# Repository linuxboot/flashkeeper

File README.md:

# Flashkeeper

## Manage and Protect your SPI Flash Chip!

[Documentation](https://flashkeeper.org) | [Source](https://git.15h.org/Flashkeeper/flashkeeper) | [Join us on Matrix!](https://matrix.to/#/#flashkeeper:matrix.org)

Flashkeeper is a family of open-hardware add-ons for standard SOIC-8 and WSON-8 SPI NOR flash chips (as are commonly used for firmware storage in PCs and other electronics), providing functionality for write-protection control, SPI bus breakout, flash device emulation, reprogramming, and state validation.

Flashkeeper development takes place on the [15h.org](https://15h.org) Git forge, and is mirrored to Github as a backup. If you wish to participate in Flashkeeper development on 15h.org infrastructure, please request an account in either the [Flashkeeper room](https://matrix.to/#/#flashkeeper:matrix.org) or the 15h.org room on Matrix. Issues may be opened on either 15h.org or Github.

For user information, please see the [documentation](https://flashkeeper.org). For hardware source files, see `hw/`.

The Flashkeeper project is supported by [NLnet NGI Zero Core](https://nlnet.nl/project/Flashkeeper/).

---

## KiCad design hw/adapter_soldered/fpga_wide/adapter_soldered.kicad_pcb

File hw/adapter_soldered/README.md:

# Soldered Chip Adapter

`wp_only_wide`: Write-protect-only chip adapter, controls flash chip write protect using switch or solder jumper, for wide (standard for flash chips) SOIC-8 and WSON-8.

`wp_only`: Same as above, for (rare for flash chips) "narrow" SOIC-8 packages

`breakout_wide`: Breakout chip adapter, for connecting your flash chip to external hardware (like a programmer or an SPIspy device) using a 0.5mm 8-pin FFC. For wide SOIC-8 and WSON-8.

`integrated_cable`: Experimental. Like the breakout adapter, but rather than having an FFC ZIF socket like the above, it has a short length of FFC built-in.

`adapter_soldered.kicad_pro` Overarching KiCAD project containing all variants. Use of this is optional.

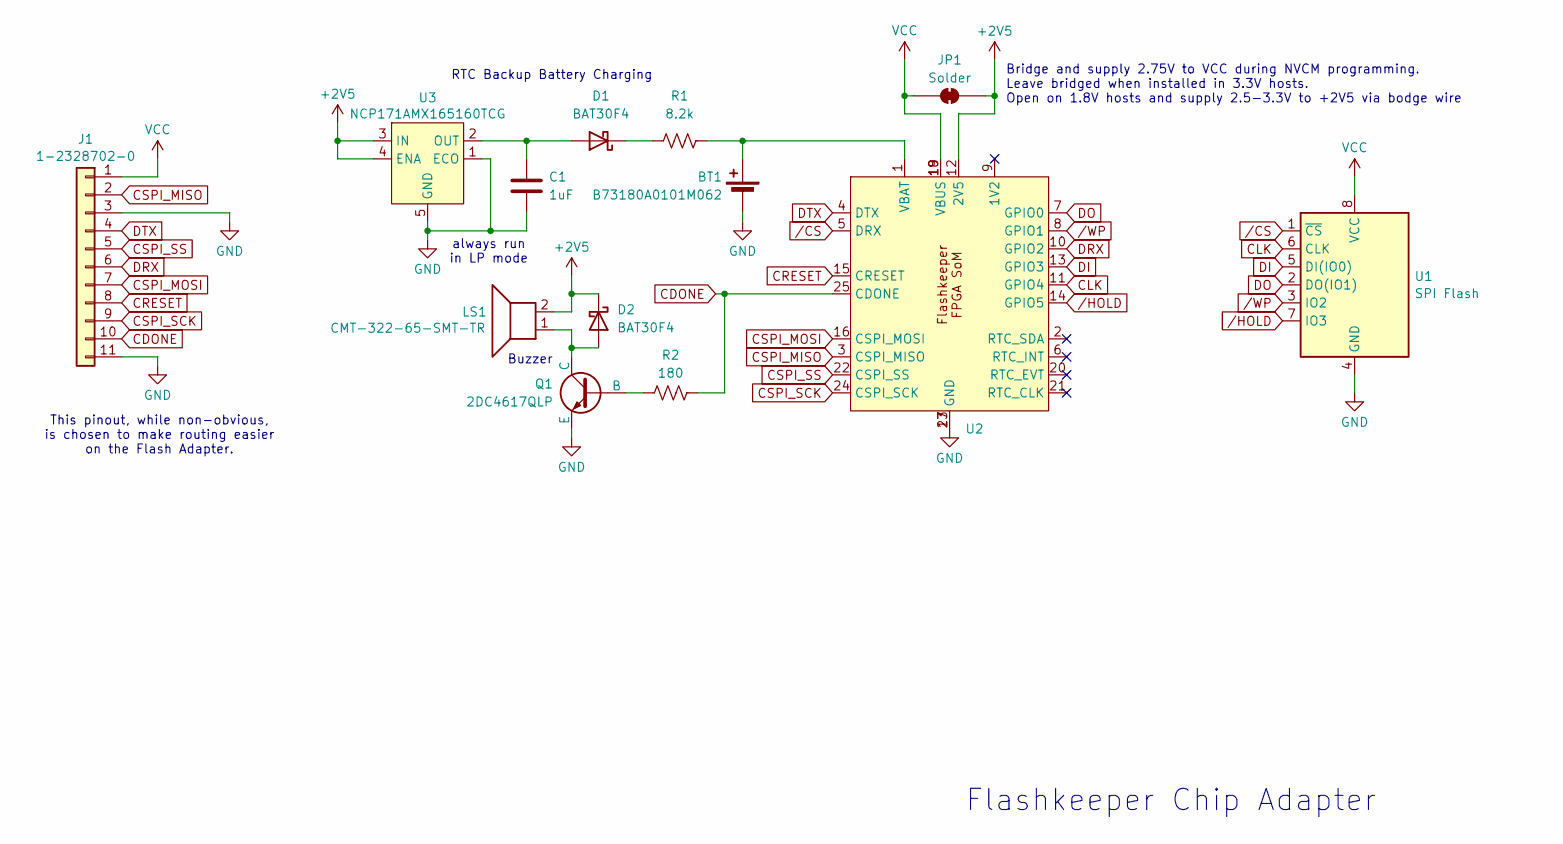
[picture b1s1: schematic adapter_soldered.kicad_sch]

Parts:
BT1: B73180A0101M062; C_1812_4532Metric
C1: 1uF; C_0201_0603Metric
D1, D2: BAT30F4; D_0201_0603Metric
J1: 1-2328702-0; TE_1-2328702-0
JP1: Solder; SolderJumper_0.4mm
LS1: CMT-322-65-SMT-TR; XDCR_CMT-322-65-SMT-TR
Q1: 2DC4617QLP; Diodes_DFN1006-3
R1: 8.2k; R_0201_0603Metric
R2: 180; R_0201_0603Metric
U1: SPI Flash; SolderConnector_SOIC8Wide_1.5mmLift
U2: FlashkeeperFPGASoM_ReducedPins
U3: NCP171AMX165160TCG; VREG_NCP171AMX180175TCG

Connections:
+2V5: D2.1 (K), JP1.2 (B), LS1.2, U2.12 (2V5), U3.3 (IN), U3.4 (ENA)
CDONE: J1.10, R2.2, U2.25 (CDONE)
CLK: U1.6 (CLK), U2.11 (GPIO4)
CRESET: J1.8, U2.15 (CRESET)
CSPI_MISO: J1.2, U2.3 (CSPI_MISO)
CSPI_MOSI: J1.7, U2.16 (CSPI_MOSI)
CSPI_SCK: J1.9, U2.24 (CSPI_SCK)
CSPI_SS: J1.5, U2.22 (CSPI_SS)
DI: U1.5 (DI(IO0)), U2.13 (GPIO3)
DO: U1.2 (DO(IO1)), U2.7 (GPIO0)
DRX: J1.6, U2.10 (GPIO2)
DTX: J1.4, U2.4 (DTX)
GND: BT1.2 (-), C1.2, J1.3, J1.11, Q1.3 (E), U1.4 (GND), U2.17 (GND), U2.23 (GND), U3.1 (ECO), U3.5 (GND)
unnamed: BT1.1 (+), R1.2, U2.1 (VBAT)
unnamed: C1.1, D1.2 (A), U3.2 (OUT)
unnamed: D1.1 (K), R1.1
unnamed: D2.2 (A), LS1.1, Q1.1 (C)
unnamed: Q1.2 (B), R2.1
VCC: J1.1, JP1.1 (A), U1.8 (VCC), U2.18 (VBUS), U2.19 (VBUS)
/CS: U1.1 (~CS), U2.5 (DRX)
/HOLD: U1.7 (IO3), U2.14 (GPIO5)
/WP: U1.3 (IO2), U2.8 (GPIO1)

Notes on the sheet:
RTC Backup Battery Charging
Flashkeeper Chip Adapter
always run in LP mode
Bridge and supply 2.75V to VCC during NVCM programming. Leave bridged when installed in 3.3V hosts. Open on 1.8V hosts and supply 2.5-3.3V to +2V5 via bodge wire
Buzzer
This pinout, while non-obvious, is chosen to make routing easier on the Flash Adapter.

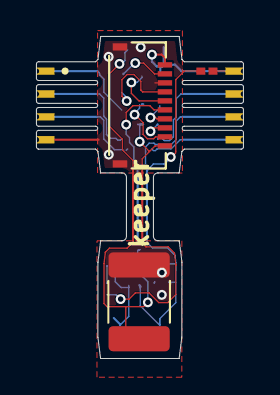
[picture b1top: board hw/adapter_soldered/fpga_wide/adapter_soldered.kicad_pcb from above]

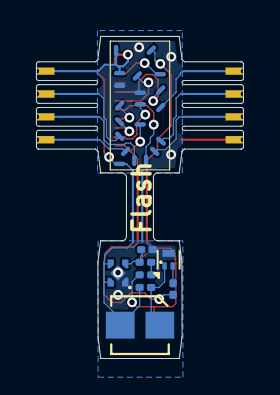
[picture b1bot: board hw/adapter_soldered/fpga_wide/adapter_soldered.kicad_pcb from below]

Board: 2 copper layers, 11.5 x 17.9 mm, 13 parts (9 on the bottom side), 22 nets.

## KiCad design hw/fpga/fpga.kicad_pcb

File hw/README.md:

# Flashkeeper Hardware
For source of the Flashkeeper website, see https://github.com/linuxboot/flashkeeper.

`adapter_soldered`: KiCAD files for the soldered Flashkeeper chip adapter

`dummy_board`: Rigid PCB with multiple flash package footprints and connectors for testing and development

`spispy_board`: FPGA-SoM-based board to run `spispy` during development

`single_stencil`: Project containing all PCBs in a single file. Intended to export a single paste-layer Gerber so that all Flashkeeper boards can be made using different parts of a single solder paste stencil.

`CAD`: FreeCAD files for Flashkeeper mechanical components

`flashkeeper.kicad_sym`: Symbol library for components used in Flashkeeper

`flashkeeper.pretty`: Footprint library for components used in Flashkeeper

KiCAD and FreeCAD files are for the latest upstream versions of KiCAD and FreeCAD, as of the last modification of that file. Depending on which versions your OS's packages ship, on some platforms (like Debian), this may mean installing from another repository (e.g. Debian Backports), or using an alternative packaging system such as Flatpak or AppImage. Please follow the installation instructions for your platform here:

- https://www.kicad.org/download/

- https://www.freecad.org/downloads.php

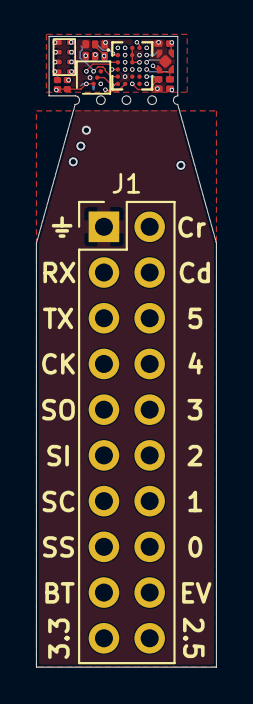
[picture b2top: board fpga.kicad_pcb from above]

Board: 6 copper layers, 10.0 x 35.0 mm, 37 parts (0 on the bottom side), 24 nets.

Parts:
C1, C2, C3, C4: 4.7 uF; C_Smaller_0201
J1: Conn_02x09_Odd_Even; PinHeader_2x10_P2.54mm_Vertical
R1: 10k; R_Smaller_0201
R3: 100; R_Smaller_0201
RN1: 10k; YC102
TP1, TP2, TP3, TP4, TP5, TP6, TP7, TP8, TP9, TP10, TP11, TP12, TP13, TP14, TP15, TP16, TP17, TP18, TP19, TP20, TP21, TP23, TP24, TP25, TP26: FPGACenterPad
U1: ICE40UP5K-UWG30ITR; BGA30N40P5X6_253X211X60N
U2: TPS7A2012PDQNR; Texas_X2SON-4_1x1mm_P0.65mm
U3: AT25DF041B-UUN-T; WLCSP-8_1.58x1.63x0.35mm_Layout3x5_P0.35x0.4mm_Ball0.25mm_P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
U4: RV-3028-C8

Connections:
+1V2: C2.1, R3.1, TP20.1, U1.C2 (VCC), U2.1 (OUT)
+2V5: C4.2, J1.20, TP19.1, U1.D4 (VPP_2V5)
CDONE: J1.4, TP1.1, U1.D3 (IOB_12A/G4_~CDONE)
CLK: J1.7, TP11.1, U1.F2 (IOB_25B/G3), U4.1 (CLKOUT)
CRESET: J1.2, R1.2, TP18.1, U1.F3 (~CRESET_B)
CSPI_MISO: J1.11, TP13.1, U1.E1 (IOB_33B/SPI_SI), U3.C3 (SO/IO1)
CSPI_MOSI: J1.9, TP12.1, U1.F1 (IOB_32A/SPI_SO), U3.D2 (SI/IO0)
CSPI_SCK: J1.13, TP14.1, U1.D1 (IOB_34A/SPI_SCK), U3.E1 (SCK), U4.3 (SCL)
CSPI_SS: J1.15, RN1.4 (R2.2), TP15.1, U1.C1 (IOB_35B/SPI_SS_B), U3.A3 (~CS)
DRX: J1.3, TP10.1, U1.A1 (IOT_36B)
DTX: J1.5, TP17.1, U1.B1 (IOB_24A)
EVT: J1.18, RN1.2 (R1.2), TP23.1, U4.8 (EVI)
GND: C1.2, C2.2, C3.1, C4.1, J1.1, TP16.1, TP25.1, U1.B4 (GND), U1.E2 (GND), U2.2 (GND), U2.5 (Pad), U3.B2 (GND), U4.5 (VSS)
GPIO0: J1.16, TP2.1, U1.A5 (RGB0)
GPIO1: J1.14, TP3.1, U1.B5 (RGB1)
GPIO2: J1.12, TP4.1, U1.C5 (RGB2)
GPIO3: J1.10, TP5.1, U1.E5 (IOB_0A)
GPIO4: J1.8, TP6.1, U1.D5 (IOB_2A)
GPIO5: J1.6, TP7.1, U1.F5 (IOB_3B/G6)
unnamed: C1.1, R3.2, U1.B2 (VCCPLL)
RTC_INT: TP8.1, U1.A4 (IOT_47A), U4.2 (~INT)
RTC_SDA: TP24.1, U1.A2 (IOT_37A), U4.4 (SDA)
VBAT: J1.17, TP21.1, U4.6 (VBACKUP)
VBUS: C3.2, J1.19, R1.1, RN1.1 (R1.1), RN1.3 (R2.1), TP9.1, TP26.1, U1.A3 (VCCIO_0), U1.B3 (IOT_46B/G0), U1.C3 (IOB_10A), U1.C4 (VCCIO_2), U1.D2 (SPI_VCCIO1), U2.3 (EN), U2.4 (IN), U3.A1 (VCC), U3.C1 (~HOLD), U4.7 (VDD)

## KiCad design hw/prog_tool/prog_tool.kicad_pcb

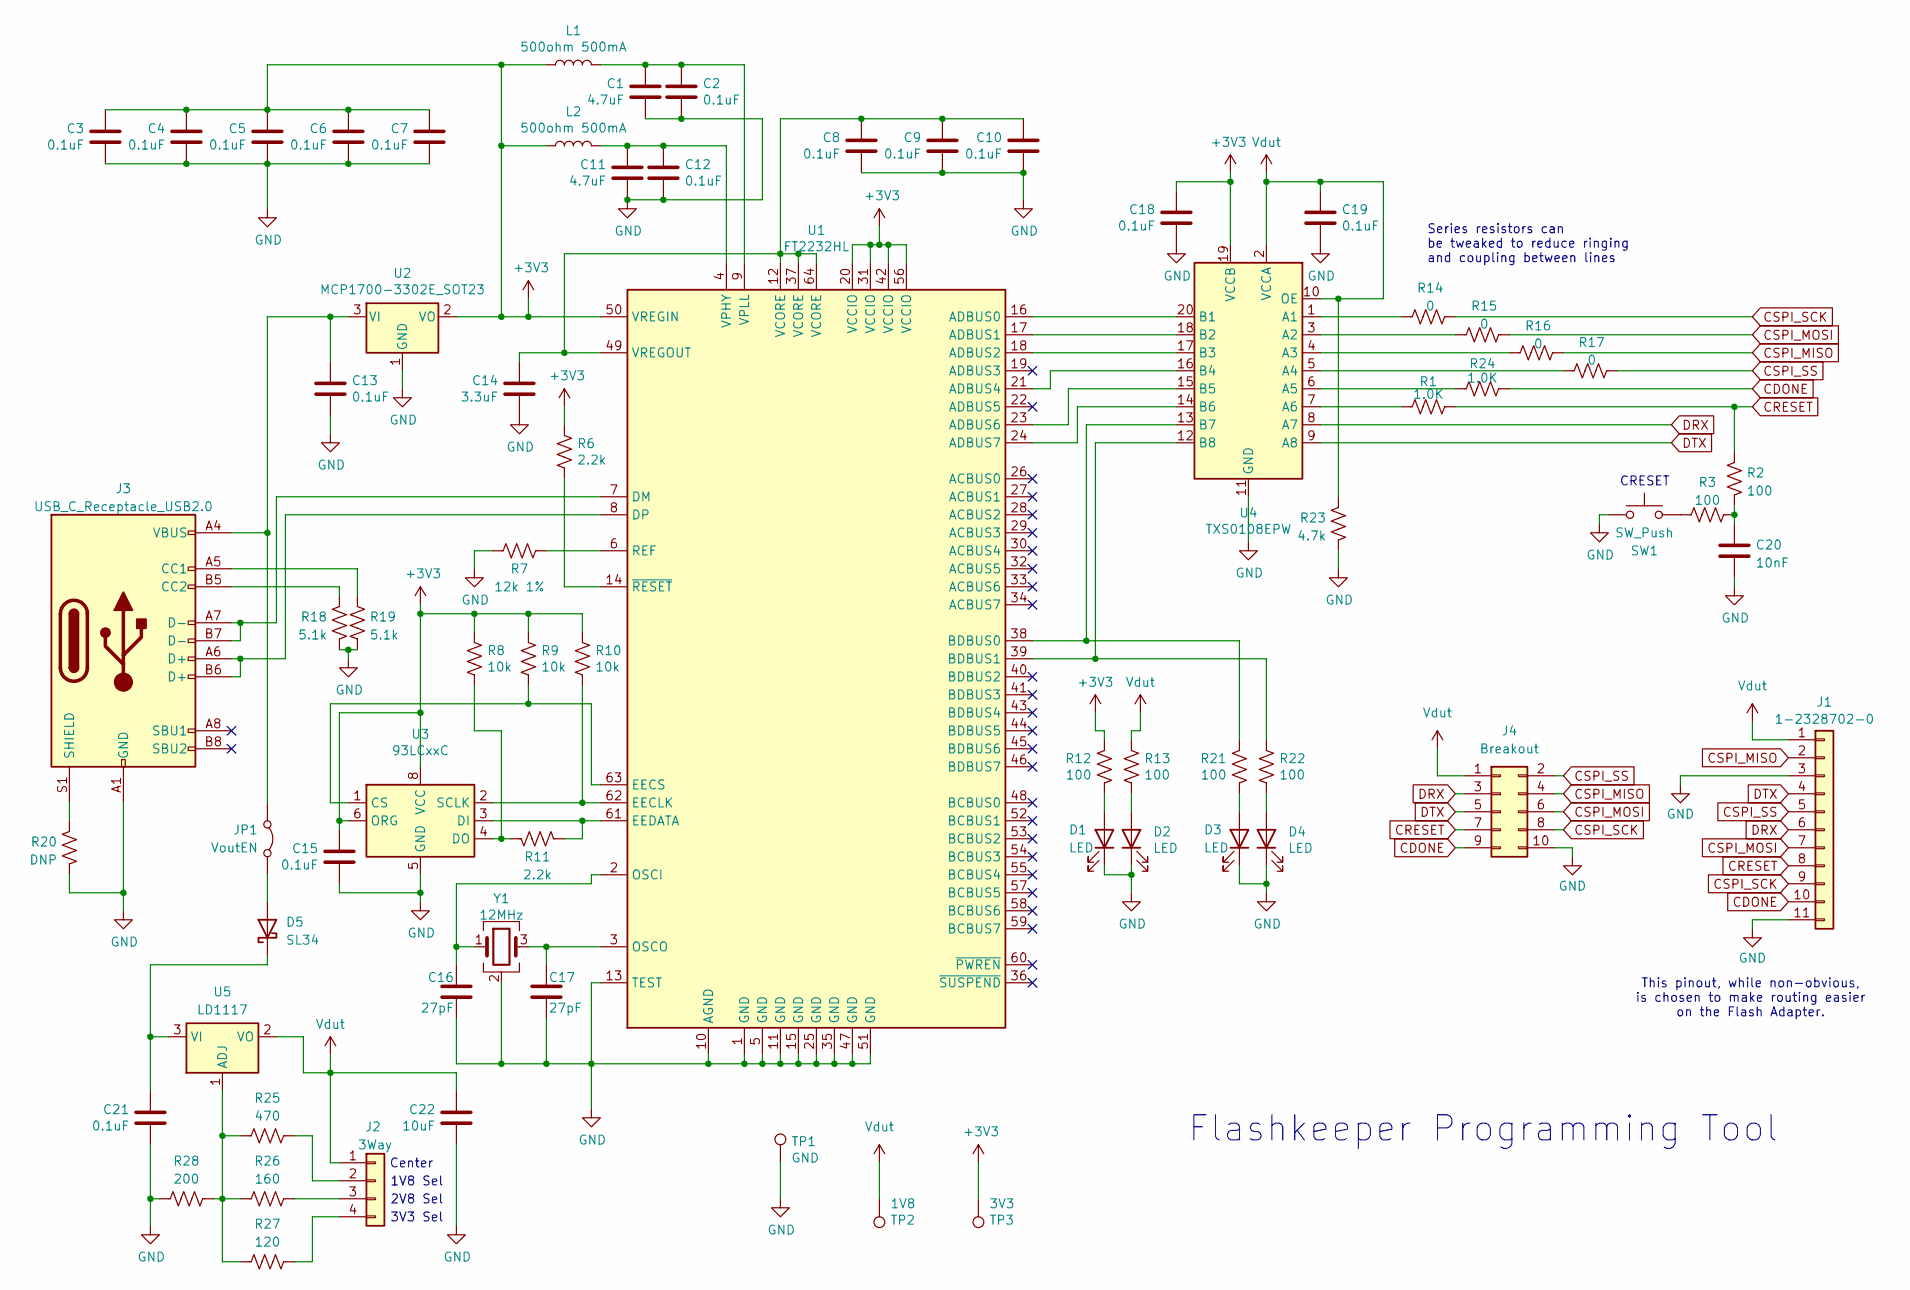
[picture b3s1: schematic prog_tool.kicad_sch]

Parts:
C1, C11: 4.7uF; C_0603_1608Metric
C2, C3, C4, C5, C6, C7, C8, C9, C10, C12, C13, C15, C18, C19, C21: 0.1uF; C_0603_1608Metric
C14: 3.3uF; C_0603_1608Metric
C16, C17: 27pF; C_0603_1608Metric
C20: 10nF; C_0603_1608Metric
C22: 10uF; C_0603_1608Metric
D1, D2, D3, D4: LED; LED_0603_1608Metric
D5: SL34; D_SMA
J1: 1-2328702-0; TE_1-2328702-0
J2: 3Way; ThreeWayJumper
J3: USB_C_Receptacle_USB2.0; USB4215-03-A
J4: Breakout; PinHeader_2x05_P2.54mm_Vertical
JP1: VoutEN; PinHeader_1x02_P2.54mm_Vertical
L1, L2: 500ohm 500mA; L_0603_1608Metric
R1, R24: 1.0K; R_0603_1608Metric
R2, R3, R12, R13, R21, R22: 100; R_0603_1608Metric
R6, R11: 2.2k; R_0603_1608Metric
R7: 12k 1%; R_0603_1608Metric
R8, R9, R10: 10k; R_0603_1608Metric
R14, R15, R16, R17: 0; R_0603_1608Metric
R18, R19: 5.1k; R_0603_1608Metric
R20: DNP; R_0603_1608Metric
R23: 4.7k; R_0603_1608Metric
R25: 470; R_0603_1608Metric
R26: 160; R_0603_1608Metric
R27: 120; R_0603_1608Metric
R28: 200; R_0603_1608Metric
SW1: SW_Push; SW_PUSH_6mm
TP1: GND; TestPoint_THTPad_2.0x2.0mm_Drill1.0mm
TP2: 1V8; TestPoint_THTPad_2.0x2.0mm_Drill1.0mm
TP3: 3V3; TestPoint_THTPad_2.0x2.0mm_Drill1.0mm
U1: FT2232HL; LQFP-64_10x10mm_P0.5mm
U2: MCP1700-3302E_SOT23; SOT-23
U3: 93LCxxC; SOIC-8_3.9x4.9mm_P1.27mm
U4: TXS0108EPW; TSSOP-20_4.4x6.5mm_P0.65mm
U5: LD1117; SOT-223-3_TabPin2
Y1: 12MHz; Crystal_SMD_3225-4Pin_3.2x2.5mm

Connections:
+3V3: C3.2, C4.2, C5.2, C6.2, C7.2, C15.2, C18.2, L1.1, L2.1, R6.1, R8.1, R9.1, R10.1, R12.2, TP3.1 (1_1), U1.20 (VCCIO), U1.31 (VCCIO), U1.42 (VCCIO), U1.50 (VREGIN), U1.56 (VCCIO), U2.2 (VO), U3.6 (ORG), U3.8 (VCC), U4.19 (VCCB)
CDONE: J1.10, J4.9, R24.2
CRESET: J1.8, J4.7, R1.2, R2.1
CSPI_MISO: J1.2, J4.4, R16.1
CSPI_MOSI: J1.7, J4.6, R15.1
CSPI_SCK: J1.9, J4.8, R14.1
CSPI_SS: J1.5, J4.2, R17.1
DRX: J1.6, J4.3, U4.8 (A7)
DTX: J1.4, J4.5, U4.9 (A8)
GND: C1.1, C2.2, C3.1, C4.1, C5.1, C6.1, C7.1, C8.1, C9.1, C10.1, C11.1, C12.2, C13.2, C14.1, C15.1, C16.1, C17.1, C18.1, C19.2, C20.2, C21.1, C22.1, D1.1 (K), D2.1 (K), D3.1 (K), D4.1 (K), J1.3, J1.11, J3.A1 (GND), J3.A12 (GND), J3.B1 (GND), J3.B12 (GND), J4.10, R7.2, R18.1, R19.2, R20.1, R23.1, R28.1, SW1.2, TP1.1 (1_1), U1.1 (GND), U1.5 (GND), U1.10 (AGND), U1.11 (GND), U1.13 (TEST), U1.15 (GND), U1.25 (GND), U1.35 (GND), U1.47 (GND), U1.51 (GND), U2.1 (GND), U3.5 (GND), U4.11 (GND), Y1.2 (G), Y1.4 (G)
unnamed: C20.1, R2.2, R3.2
unnamed: D1.2 (A), R12.1
unnamed: D2.2 (A), R13.2
unnamed: D3.2 (A), R21.1
unnamed: D4.2 (A), R22.2
unnamed: D5.2 (A), JP1.1 (A)
unnamed: C21.2, D5.1 (K), U5.3 (VI)
unnamed: J2.2, R25.2
unnamed: J2.3, R26.2
unnamed: J2.4, R27.2
unnamed: J3.A5 (CC1), R19.1
unnamed: J3.B5 (CC2), R18.2
unnamed: J3.S1 (SHIELD), R20.2
unnamed: C13.1, J3.A4 (VBUS), J3.A9 (VBUS), J3.B4 (VBUS), J3.B9 (VBUS), JP1.2 (B), U2.3 (VI)
unnamed: R3.1, SW1.1
unnamed: U1.16 (ADBUS0), U4.20 (B1)
unnamed: U1.17 (ADBUS1), U4.18 (B2)
unnamed: U1.18 (ADBUS2), U4.17 (B3)
unnamed: U1.21 (ADBUS4), U4.16 (B4)
unnamed: U1.23 (ADBUS6), U4.15 (B5)
unnamed: U1.24 (ADBUS7), U4.14 (B6)
unnamed: R21.2, U1.38 (BDBUS0), U4.13 (B7)
unnamed: R22.1, U1.39 (BDBUS1), U4.12 (B8)
unnamed: J3.A7 (D-), J3.B7 (D-), U1.7 (DM)
unnamed: J3.A6 (D+), J3.B6 (D+), U1.8 (DP)
unnamed: R10.2, U1.62 (EECLK), U3.2 (SCLK)
unnamed: R9.2, U1.63 (EECS), U3.1 (CS)
unnamed: R11.2, U1.61 (EEDATA), U3.3 (DI)
unnamed: C16.2, U1.2 (OSCI), Y1.1
unnamed: C17.2, U1.3 (OSCO), Y1.3
unnamed: R7.1, U1.6 (REF)
unnamed: C11.2, C12.1, L2.2, U1.4 (VPHY)
unnamed: C1.2, C2.1, L1.2, U1.9 (VPLL)
unnamed: C8.2, C9.2, C10.2, C14.2, U1.12 (VCORE), U1.37 (VCORE), U1.49 (VREGOUT), U1.64 (VCORE)
unnamed: R6.2, U1.14 (~RESET)
unnamed: R8.2, R11.1, U3.4 (DO)
unnamed: R14.2, U4.1 (A1)
unnamed: R15.2, U4.3 (A2)
unnamed: R16.2, U4.4 (A3)
unnamed: R17.2, U4.5 (A4)
unnamed: R24.1, U4.6 (A5)
unnamed: R1.1, U4.7 (A6)
unnamed: R25.1, R26.1, R27.1, R28.2, U5.1 (ADJ)
Vdut: C19.1, C22.2, J1.1, J2.1, J4.1, R13.1, R23.2, TP2.1 (1_1), U4.2 (VCCA), U4.10 (OE), U5.2 (VO)

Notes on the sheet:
1V8 Sel
Center
This pinout, while non-obvious, is chosen to make routing easier on the Flash Adapter.
3V3 Sel
Flashkeeper Programming Tool
2V8 Sel
CRESET
Series resistors can be tweaked to reduce ringing and coupling between lines

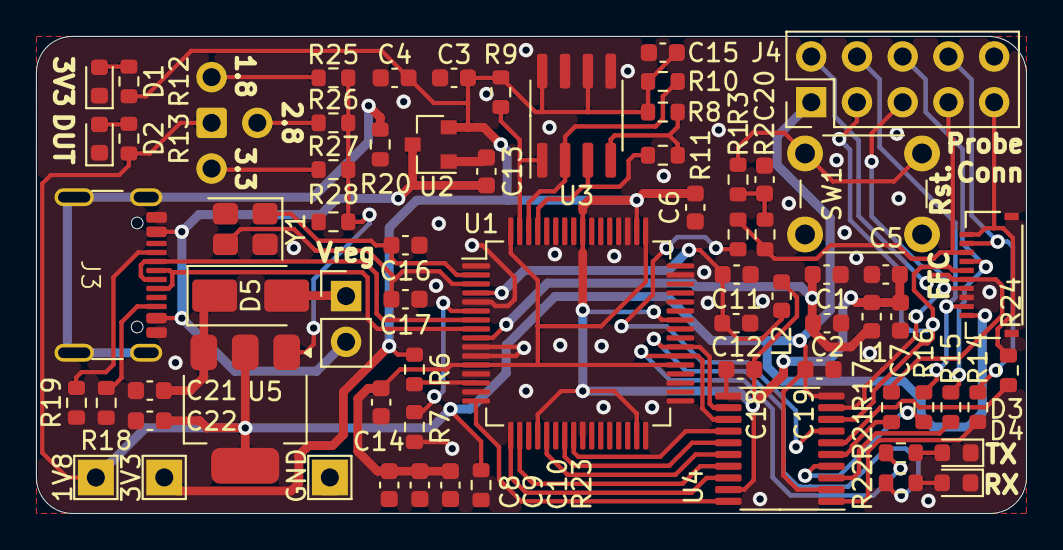
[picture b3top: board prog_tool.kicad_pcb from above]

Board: 2 copper layers, 55.0 x 26.5 mm, 70 parts (0 on the bottom side), 54 nets.

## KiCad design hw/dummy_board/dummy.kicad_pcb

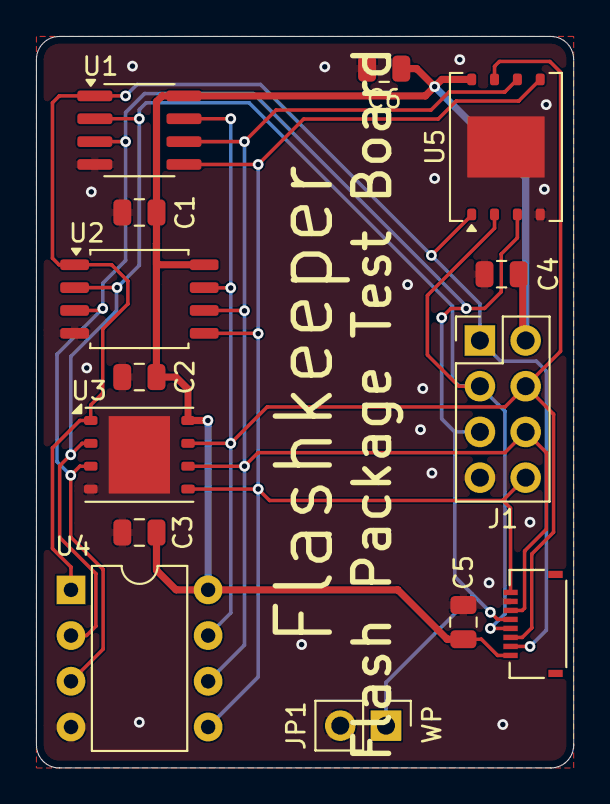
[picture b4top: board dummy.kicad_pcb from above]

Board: 2 copper layers, 29.8 x 40.6 mm, 14 parts (0 on the bottom side), 8 nets.

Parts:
C1, C2, C3, C4, C5, C6: 0.1uF; C_0805_2012Metric
J1: Conn_02x04; PinHeader_2x04_P2.54mm_Vertical
J2: FFC; TE_2328702-8
JP1: Jumper_2_Open; PinHeader_1x02_P2.54mm_Vertical
U1: W25Q128JVS; SOIC-8_3.9x4.9mm_P1.27mm
U2: W25Q128JVS; SOIC-8_5.23x5.23mm_P1.27mm
U3: W25Q128JVP; WSON-8-1EP_6x5mm_P1.27mm_EP3.4x4.3mm
U4: W25Q128JVS; DIP-8_W7.62mm
U5: W25Q128JVP; WSON-8-1EP_8x6mm_P1.27mm_EP3.4x4.3mm

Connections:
CLK: J1.6, J2.6, U1.6 (CLK), U2.6 (CLK), U3.6 (CLK), U4.6 (CLK), U5.6 (CLK)
CS: J1.1, J2.2, U1.1 (~CS), U2.1 (~CS), U3.1 (~CS), U4.1 (~CS), U5.1 (~CS)
DI: J1.8, J2.8, U1.5 (DI(IO0)), U2.5 (DI(IO0)), U3.5 (DI(IO0)), U4.5 (DI(IO0)), U5.5 (DI(IO0))
DO: J1.3, J2.4, U1.2 (DO(IO1)), U2.2 (DO(IO1)), U3.2 (DO(IO1)), U4.2 (DO(IO1)), U5.2 (DO(IO1))
GND: C1.2, C2.2, C3.2, C4.2, C5.2, C6.2, J1.7, J2.7, JP1.2 (B), U1.4 (GND), U2.4 (GND), U3.4 (GND), U3.9 (GND), U4.4 (GND), U5.4 (GND), U5.9 (GND)
IO2: J1.5, J2.5, JP1.1 (A), U1.3 (IO2), U2.3 (IO2), U3.3 (IO2), U4.3 (IO2), U5.3 (IO2)
IO3: J1.4, J2.3, U1.7 (IO3), U2.7 (IO3), U3.7 (IO3), U4.7 (IO3), U5.7 (IO3)
VCC: C1.1, C2.1, C3.1, C4.1, C5.1, C6.1, J1.2, J2.1, U1.8 (VCC), U2.8 (VCC), U3.8 (VCC), U4.8 (VCC), U5.8 (VCC)

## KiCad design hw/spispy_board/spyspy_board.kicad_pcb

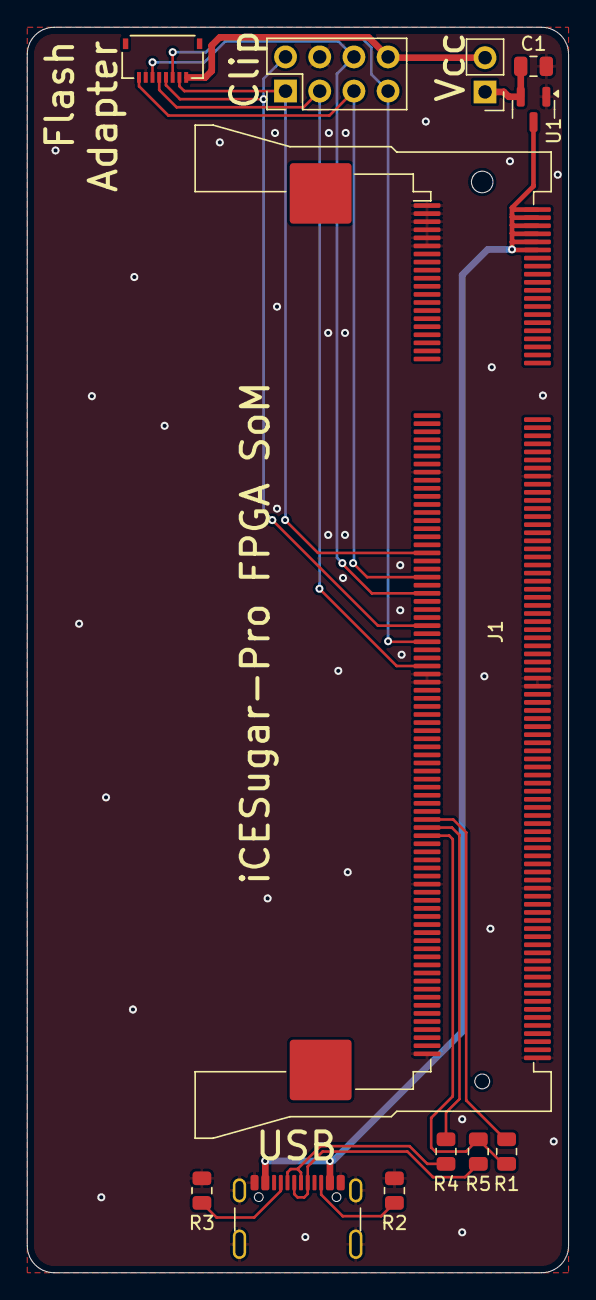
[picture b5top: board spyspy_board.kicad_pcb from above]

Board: 2 copper layers, 40.2 x 92.5 mm, 12 parts (0 on the bottom side), 17 nets.

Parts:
C1: 0.1uF; C_0805_2012Metric
J1: SODIMM-200; TE_DDR2-SODIMM-200_1565918-4
J2: USB_C_Receptacle_USB2.0_16P; USB4215-03-A
J3: Header_2x4; PinHeader_2x04_P2.54mm_Vertical
J4: FFC; TE_2328702-8
JP1: Jumper_2_Bridged; PinHeader_1x02_P2.54mm_Vertical
R1: 1.5k; R_0805_2012Metric
R2, R3: 5.1k; R_0805_2012Metric
R4, R5: 27; R_0805_2012Metric
U1: MCP1700x-330xxTT; SOT-23

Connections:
+3V3: C1.1, JP1.1 (A), U1.2 (VO)
+5V: J1.2, J1.4, J1.6, J1.8, J1.10, J1.12, J2.A4 (VBUS), J2.A9 (VBUS), J2.B4 (VBUS), J2.B9 (VBUS), U1.3 (VI)
CLK: J1.85, J3.6, J4.6
DI: J1.81, J3.5, J4.8
DO: J1.93, J3.2, J4.4
FPGA_D+: J1.145, R1.2, R5.1
FPGA_D+_PULL: J1.141, R1.1
FPGA_D-: J1.143, R4.1
GND: C1.2, J1.1, J1.3, J1.5, J1.7, J1.9, J1.11, J1.55, J1.56, J1.105, J1.106, J1.107, J1.108, J1.157, J1.158, J1.199, J1.200, J2.A1 (GND), J2.A12 (GND), J2.B1 (GND), J2.B12 (GND), J2.S1 (SHIELD), J3.4, J4.7, R2.2, R3.2, U1.1 (GND)
unnamed: J2.A5 (CC1), R3.1
unnamed: J2.B5 (CC2), R2.1
unnamed: J2.A6 (D+), J2.B6 (D+), R5.2
unnamed: J2.A7 (D-), J2.B7 (D-), R4.2
unnamed: J3.8, J4.1, JP1.2 (B)
/CS: J1.75, J3.1, J4.2
/HOLD: J1.97, J3.7, J4.3
/WP: J1.103, J3.3, J4.5

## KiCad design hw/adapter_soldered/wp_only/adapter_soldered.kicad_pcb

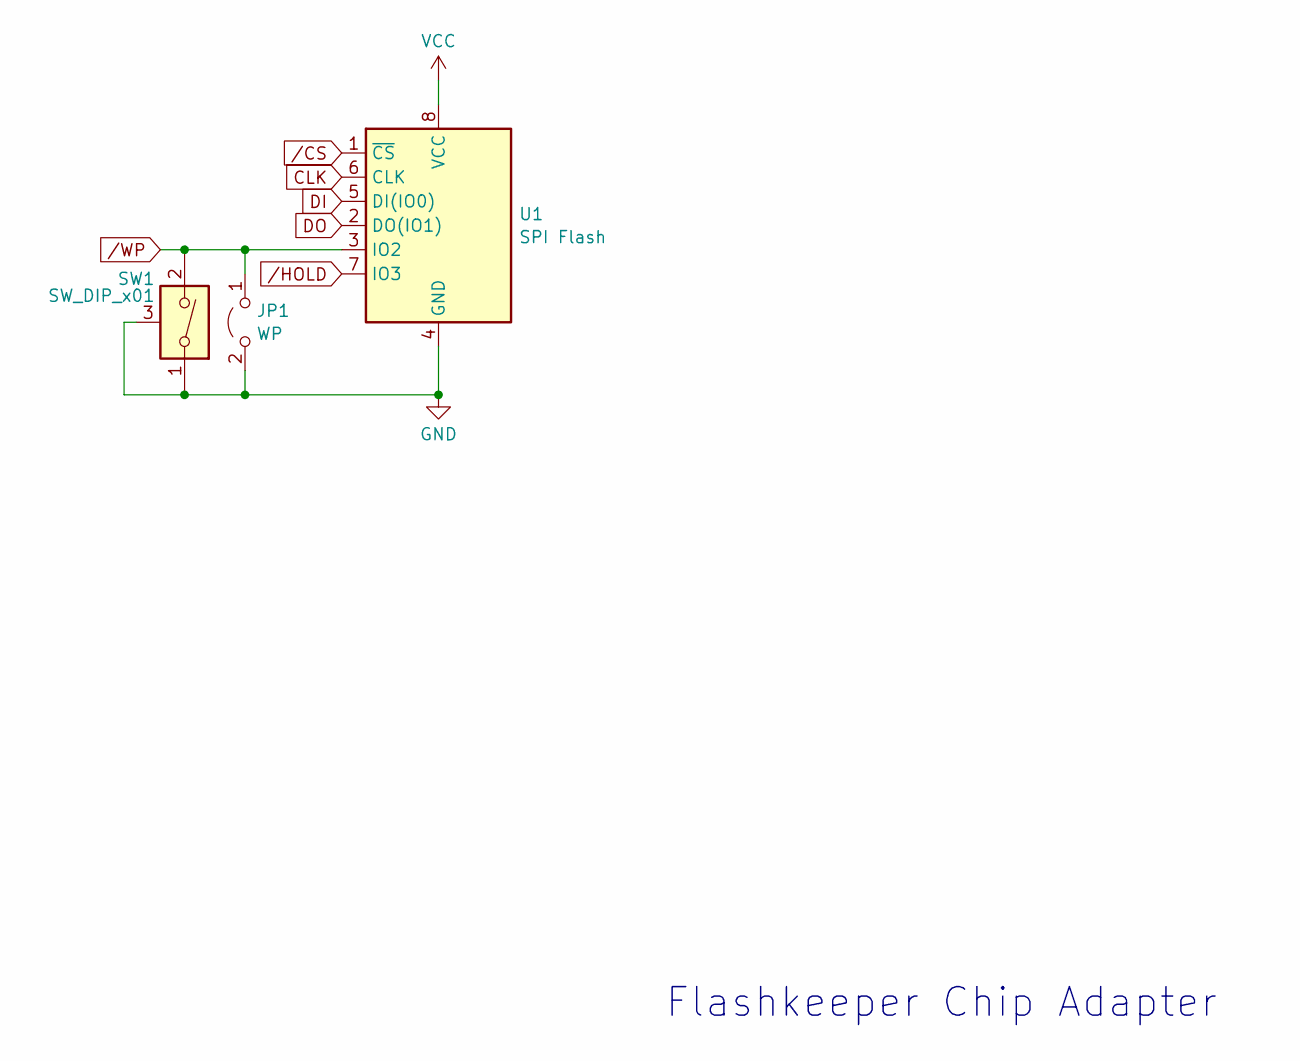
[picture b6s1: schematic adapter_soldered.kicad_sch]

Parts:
JP1: WP; SolderJumper-2_P1.3mm_Open_RoundedPad1.0x1.5mm
SW1: SW_DIP_x01; SW_DIP_SPSTx01_Slide_Copal_CVS-01xB_W5.9mm_P1mm
U1: SPI Flash; SolderConnector_SOIC8

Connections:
CLK: U1.6 (CLK)
DI: U1.5 (DI(IO0))
DO: U1.2 (DO(IO1))
GND: JP1.2 (B), SW1.1, SW1.3 (GND), U1.4 (GND)
VCC: U1.8 (VCC)
/CS: U1.1 (~CS)
/HOLD: U1.7 (IO3)
/WP: JP1.1 (A), SW1.2, U1.3 (IO2)

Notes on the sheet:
Flashkeeper Chip Adapter

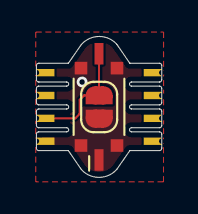
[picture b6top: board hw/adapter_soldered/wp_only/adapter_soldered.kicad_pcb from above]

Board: 2 copper layers, 7.0 x 7.8 mm, 3 parts (0 on the bottom side), 2 nets.

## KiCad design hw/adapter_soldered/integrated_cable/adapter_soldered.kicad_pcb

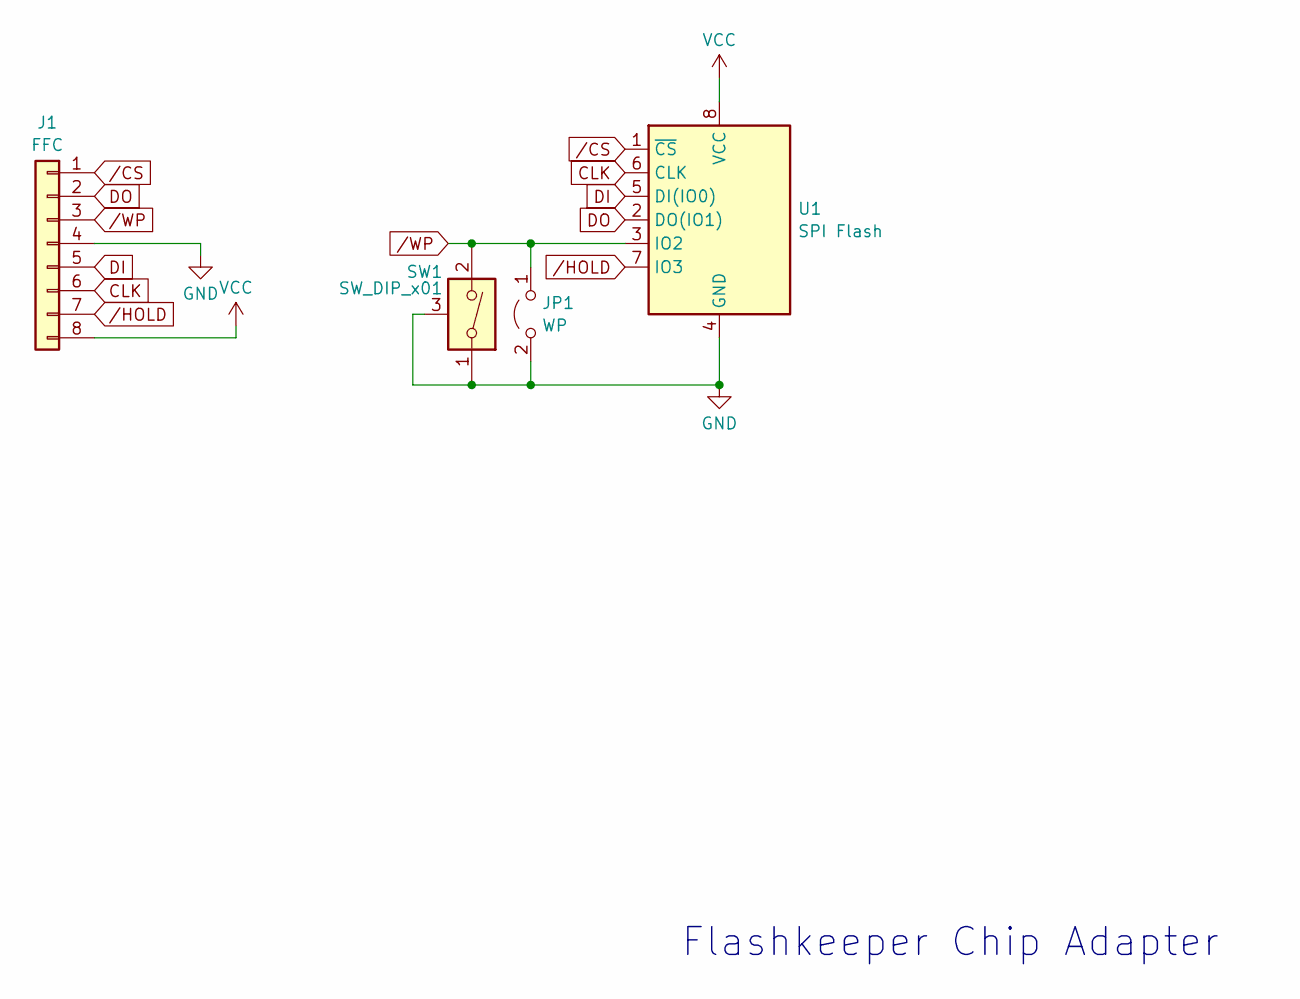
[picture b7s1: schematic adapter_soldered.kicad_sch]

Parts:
J1: FFC; FFC_8_0.5mm
JP1: WP; SolderJumper-2_P1.3mm_Open_RoundedPad1.0x1.5mm
SW1: SW_DIP_x01; SW_DIP_SPSTx01_Slide_Copal_CVS-01xB_W5.9mm_P1mm
U1: SPI Flash; SolderConnector_SOIC8

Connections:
CLK: J1.6, U1.6 (CLK)
DI: J1.5, U1.5 (DI(IO0))
DO: J1.2, U1.2 (DO(IO1))
GND: J1.4, JP1.2 (B), SW1.1, SW1.3 (GND), U1.4 (GND)
VCC: J1.8, U1.8 (VCC)
/CS: J1.1, U1.1 (~CS)
/HOLD: J1.7, U1.7 (IO3)
/WP: J1.3, JP1.1 (A), SW1.2, U1.3 (IO2)

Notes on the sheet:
Flashkeeper Chip Adapter

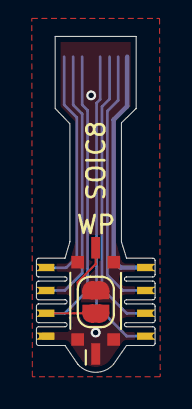
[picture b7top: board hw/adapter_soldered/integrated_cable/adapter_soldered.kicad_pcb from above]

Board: 2 copper layers, 6.6 x 18.7 mm, 4 parts (0 on the bottom side), 8 nets.

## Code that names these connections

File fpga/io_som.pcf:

# UART on DTX/DRX pins
set_io ser_rx     C5  # SOM GPIO2 - Debug UART RX
set_io ser_tx     B1  # SOM DTX - Debug UART TX

# SPI Flash
set_io flash_clk  D1  # Onboard SPI SCK
set_io flash_csb  C1  # Onboard SPI CS
set_io flash_io0  F1  # Onboard SPI MOSI
set_io flash_io1  E1  # Onboard SPI MISO

# reserved: 4-line SPI not brought out on the SoM (see top.v port list)
#set_io hspi_io2   B5  # SOM GPIO1 - host SPI IO2/WP (optional)
#set_io hspi_io3   F5  # SOM GPIO5 - host SPI IO3/HOLD (optional)
set_io hspi_io1   A5  # SOM GPIO0 - host SPI MISO
set_io hspi_io0   E5  # SOM GPIO3 - host SPI MOSI
set_io hspi_clk   D5  # SOM GPIO4 - host SPI CLK
set_io hspi_csb   A1  # SOM DRX - host SPI CS

# LED indicator (reused CDONE pin)
set_io led_n      D3  # Debug LED

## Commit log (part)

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2024-10-31 Update CNAME
2024-10-31 docs/*: change references from tlaurion/osresearch to linuxboot/linuxboot.org
2025-01-21 Initial soldered flash adapter version
2025-01-21 Add KiCAD 3D renderings of chip adapter flex PCB
2025-02-05 Add hardware architecture/component selection/mechanical document, add CAD for flash chips, fix gitignore for Jekyll-generated pages
2025-02-14 Add WP-only flash adapters, add component and PCB for SOIC8-W (wide) flash chips, documentation
2025-02-16 Add image to documentation index
2025-02-28 docs/Community.md: add Matrix room address under Community page
2025-04-06 Initial CAD for soldered adapter on WSON packages, WSON package validation model
2025-04-07 Add an "interposer block" between the WSON package and the chip adapter, holding the chip adapter's legs down against the sides of the WSON
2025-04-12 Add image of WSON chip and interposer block (WSON.FCstd) to website
2025-07-11 Import latest PCB changes from out-of-tree flashkeeper_hw repo
2025-07-14 More information on the wiki for end-users under Getting Started, slight wiki cleanup
2025-07-14 Fix link on website homepage
2026-05-14 Add KiCAD source for Flashkeeper FPGA SoM and its production panel and its associated component libraries. Add basic 3D models for some of the chip packages used. Minimal initial PicoSoC/PicoRV32 con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
2026-05-31 Add KiCAD for Flashkeeper FPGA module flex PCB, for use with the previously-committed FPGA SoM, and for a USB programming/configuration/debug tool for use with it. Various new component library symbo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
2026-05-31 Update documentation/website for new FPGA hardware, document cables
2026-05-31 Fix typo on website
